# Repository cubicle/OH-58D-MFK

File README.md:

# OH-58D-MFK

[![CC BY-NC-SA 4.0][cc-by-nc-sa-shield]][cc-by-nc-sa]

## Work in progress

This project is still work in progress. Print and assemble at your own risk.

## BOM

-  1 x [Arduino Uno](https://www.amazon.de/Arduino-A000066-UNO-Rev3/dp/B008GRTSV6)
- 15 x [Heat Set Inserts M3x3 (short)](https://cnckitchen.store/products/heat-set-insert-m3-x-3-short-version-100-pieces)
-  4 x Heat Set Inserts M4
- 51 x [Diode SMD 0805 1N4148](https://www.ebay.de/itm/312738927547)
-  9 x [Resistor SMD 0805 10K](https://www.ebay.de/itm/362412320635)
- 47 x [OMRON B3F-115x Tactile Switch](https://www.ebay.de/itm/231954583799)
-  2 x [Switch cover](https://www.reichelt.de/de/de/shop/produkt/sicherheitsabdeckungen_fuer_kippschalter-105434)
-  2 x [Switch ON/OFF](https://www.pollin.de/p/kippschalter-kn3-c-101a-1-polig-on-off-420068)
-  1 x [Switch (ON)/OFF/(ON)](https://www.pollin.de/p/kippschalter-kn3-c-101a-1-polig-on-off-420068)
-  Break away pin headers
-  Wire
-  [Dupont crimping tool and connectors](https://www.amazon.de/dp/B07QX51F3B)
- 10 x Screw M3x0.50 x 8
-  5 x Screw M3x0.50 x 12

## 3D printed parts

### STLs

STLs are hosted on [Printables](https://www.printables.com/model/1201023-oh-58d-mfk).

### CAD

You can find the CAD files on [Onshape](https://cad.onshape.com/documents/6787d83c44a91f8cde39e86e/w/96151ec904b149525745d522/e/fceb9b6b394f6e8ffc93c401). Be careful as these may contain untested changes.

### Arduino Uno Case

You will need to print a case for the Arduino Uno. I used the [Arduino Uno Case](https://www.printables.com/model/122097-arduino-uno-case) from [Kazik](https://www.printables.com/@Kazik).

## License

Except where otherwise noted, this work © 2025 is licensed under a [Creative Commons Attribution-NonCommercial-ShareAlike 4.0 International License][cc-by-nc-sa].

[![CC BY-NC-SA 4.0][cc-by-nc-sa-image]][cc-by-nc-sa]

[cc-by-nc-sa]: http://creativecommons.org/licenses/by-nc-sa/4.0/
[cc-by-nc-sa-image]: https://licensebuttons.net/l/by-nc-sa/4.0/88x31.png
[cc-by-nc-sa-shield]: https://img.shields.io/badge/License-CC%20BY--NC--SA%204.0-lightgrey.svg

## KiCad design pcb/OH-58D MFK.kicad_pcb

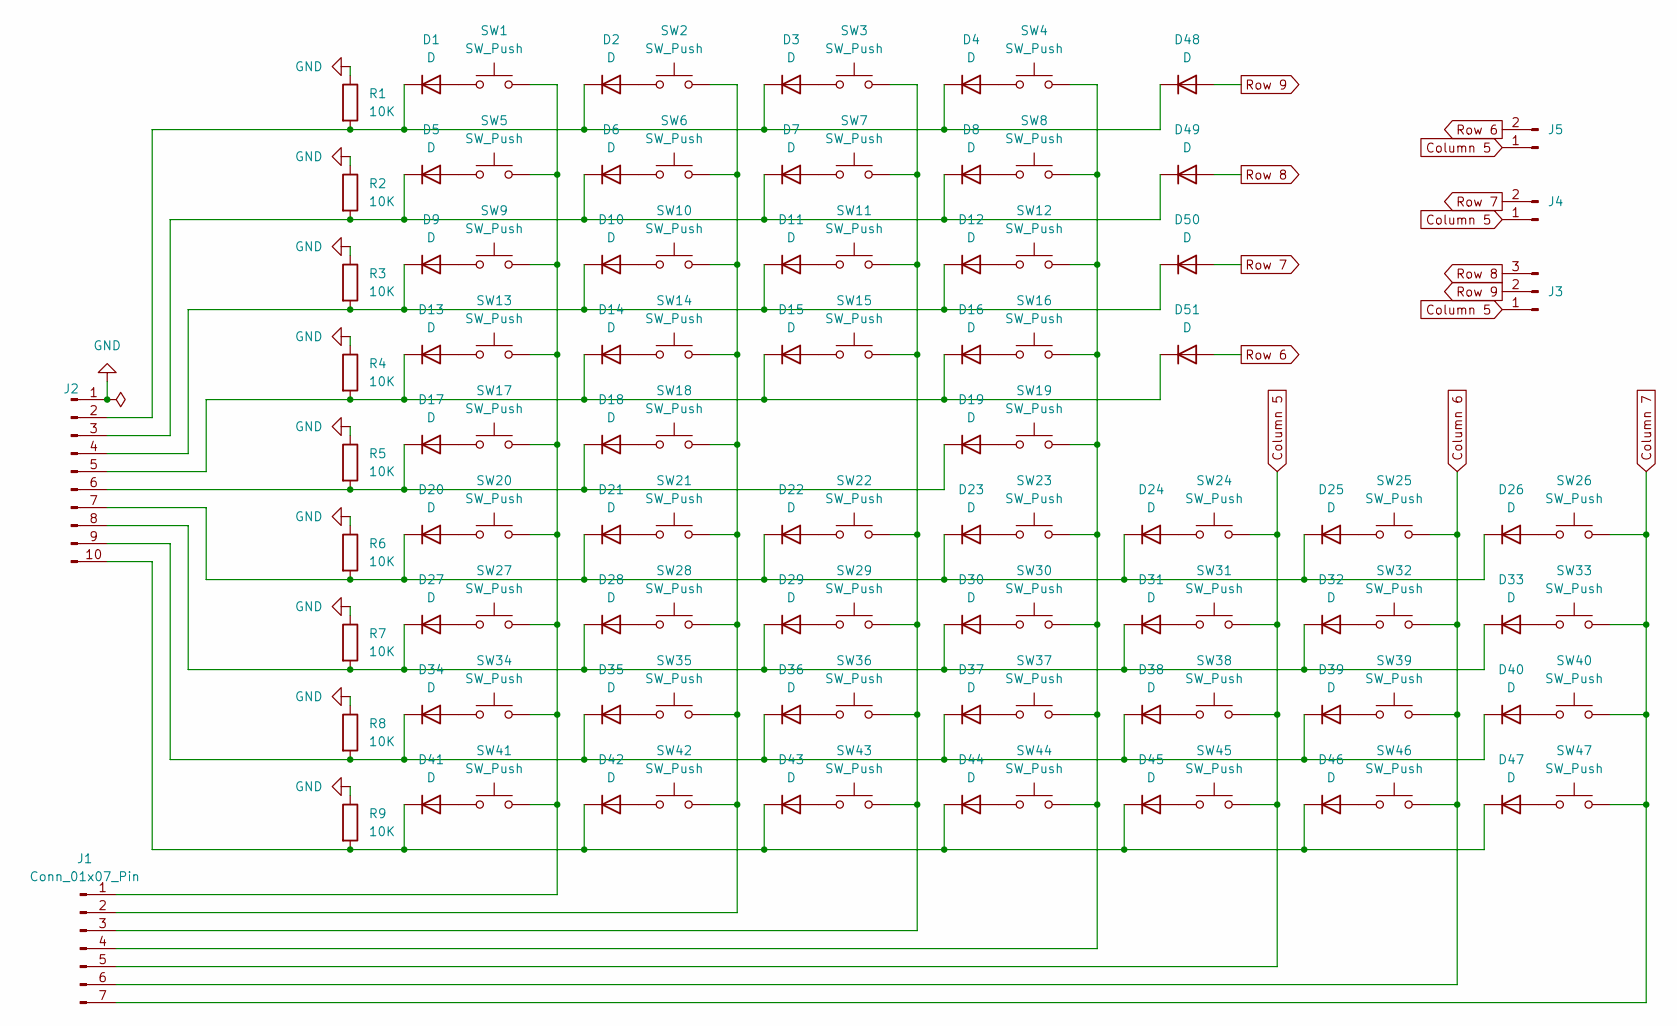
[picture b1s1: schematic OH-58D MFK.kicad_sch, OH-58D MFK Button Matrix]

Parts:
D1, D2, D3, D4, D5, D6, D7, D8, D9, D10, D11, D12, D13, D14, D15, D16, D17, D18, D19, D20, D21, D22, D23, D24, D25, D26, D27, D28, D29, D30, D31, D32, D33, D34, D35, D36, D37, D38, D39, D40, D41, D42, D43, D44, D45, D46, D47, D48, D49, D50, D51: D; D_0805_2012Metric_Pad1.15x1.40mm_HandSolder
J1: Conn_01x07_Pin; PinHeader_1x07_P2.54mm_Vertical
J2: Conn_01x10_Pin; PinHeader_1x10_P2.54mm_Vertical
J3: Conn_01x03_Pin; PinHeader_1x03_P2.54mm_Vertical
J4, J5: Conn_01x02_Pin; PinHeader_1x02_P2.54mm_Vertical
R1, R2, R3, R4, R5, R6, R7, R8, R9: 10K; R_0805_2012Metric_Pad1.20x1.40mm_HandSolder
SW1, SW2, SW3, SW4, SW5, SW6, SW7, SW8, SW9, SW10, SW11, SW12, SW13, SW14, SW15, SW16, SW17, SW18, SW19, SW20, SW21, SW22, SW23, SW24, SW25, SW26, SW27, SW28, SW29, SW30, SW31, SW32, SW33, SW34, SW35, SW36, SW37, SW38, SW39, SW40, SW41, SW42, SW43, SW44, SW45, SW46, SW47: SW_Push; SW_TH_Tactile_Omron_B3F-105x

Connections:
Column 5: J1.5, J3.1, J4.1, J5.1, SW24.2, SW31.2, SW38.2, SW45.2
Column 6: J1.6, SW25.2, SW32.2, SW39.2, SW46.2
Column 7: J1.7, SW26.2, SW33.2, SW40.2, SW47.2
GND: J2.1, R1.1, R2.1, R3.1, R4.1, R5.1, R6.1, R7.1, R8.1, R9.1
unnamed: D1.2 (A), SW1.1
unnamed: D1.1 (K), D2.1 (K), D3.1 (K), D4.1 (K), D48.1 (K), J2.2, R1.2
unnamed: D2.2 (A), SW2.1
unnamed: D3.2 (A), SW3.1
unnamed: D4.2 (A), SW4.1
unnamed: D5.2 (A), SW5.1
unnamed: D6.2 (A), SW6.1
unnamed: D7.2 (A), SW7.1
unnamed: D8.2 (A), SW8.1
unnamed: D9.2 (A), SW9.1
unnamed: D10.2 (A), SW10.1
unnamed: D9.1 (K), D10.1 (K), D11.1 (K), D12.1 (K), D50.1 (K), J2.4, R3.2
unnamed: D11.2 (A), SW11.1
unnamed: D12.2 (A), SW12.1
unnamed: D13.2 (A), SW13.1
unnamed: D13.1 (K), D14.1 (K), D15.1 (K), D16.1 (K), D51.1 (K), J2.5, R4.2
unnamed: D14.2 (A), SW14.1
unnamed: D15.2 (A), SW15.1
unnamed: D16.2 (A), SW16.1
unnamed: D17.2 (A), SW17.1
unnamed: D17.1 (K), D18.1 (K), D19.1 (K), J2.6, R5.2
unnamed: D18.2 (A), SW18.1
unnamed: D19.2 (A), SW19.1
unnamed: D20.2 (A), SW20.1
unnamed: D20.1 (K), D21.1 (K), D22.1 (K), D23.1 (K), D24.1 (K), D25.1 (K), D26.1 (K), J2.7, R6.2
unnamed: D21.2 (A), SW21.1
unnamed: D22.2 (A), SW22.1
unnamed: D23.2 (A), SW23.1
unnamed: D24.2 (A), SW24.1
unnamed: D25.2 (A), SW25.1
unnamed: D26.2 (A), SW26.1
unnamed: D27.2 (A), SW27.1
unnamed: D27.1 (K), D28.1 (K), D29.1 (K), D30.1 (K), D31.1 (K), D32.1 (K), D33.1 (K), J2.8, R7.2
unnamed: D28.2 (A), SW28.1
unnamed: D29.2 (A), SW29.1
unnamed: D30.2 (A), SW30.1
unnamed: D31.2 (A), SW31.1
unnamed: D32.2 (A), SW32.1
unnamed: D33.2 (A), SW33.1
unnamed: D34.2 (A), SW34.1
unnamed: D34.1 (K), D35.1 (K), D36.1 (K), D37.1 (K), D38.1 (K), D39.1 (K), D40.1 (K), J2.9, R8.2
unnamed: D35.2 (A), SW35.1
unnamed: D36.2 (A), SW36.1
unnamed: D37.2 (A), SW37.1
unnamed: D38.2 (A), SW38.1
unnamed: D39.2 (A), SW39.1
unnamed: D40.2 (A), SW40.1
unnamed: D41.2 (A), SW41.1
unnamed: D41.1 (K), D42.1 (K), D43.1 (K), D44.1 (K), D45.1 (K), D46.1 (K), D47.1 (K), J2.10, R9.2
unnamed: D42.2 (A), SW42.1
unnamed: D43.2 (A), SW43.1
unnamed: D44.2 (A), SW44.1
unnamed: D45.2 (A), SW45.1
unnamed: D46.2 (A), SW46.1
unnamed: D47.2 (A), SW47.1
unnamed: D5.1 (K), D6.1 (K), D7.1 (K), D8.1 (K), D49.1 (K), J2.3, R2.2
unnamed: J1.1, SW1.2, SW5.2, SW9.2, SW13.2, SW17.2, SW20.2, SW27.2, SW34.2, SW41.2
unnamed: J1.2, SW2.2, SW6.2, SW10.2, SW14.2, SW18.2, SW21.2, SW28.2, SW35.2, SW42.2
unnamed: J1.3, SW3.2, SW7.2, SW11.2, SW15.2, SW22.2, SW29.2, SW36.2, SW43.2
unnamed: J1.4, SW4.2, SW8.2, SW12.2, SW16.2, SW19.2, SW23.2, SW30.2, SW37.2, SW44.2
Row 6: D51.2 (A), J5.2
Row 7: D50.2 (A), J4.2
Row 8: D49.2 (A), J3.3
Row 9: D48.2 (A), J3.2

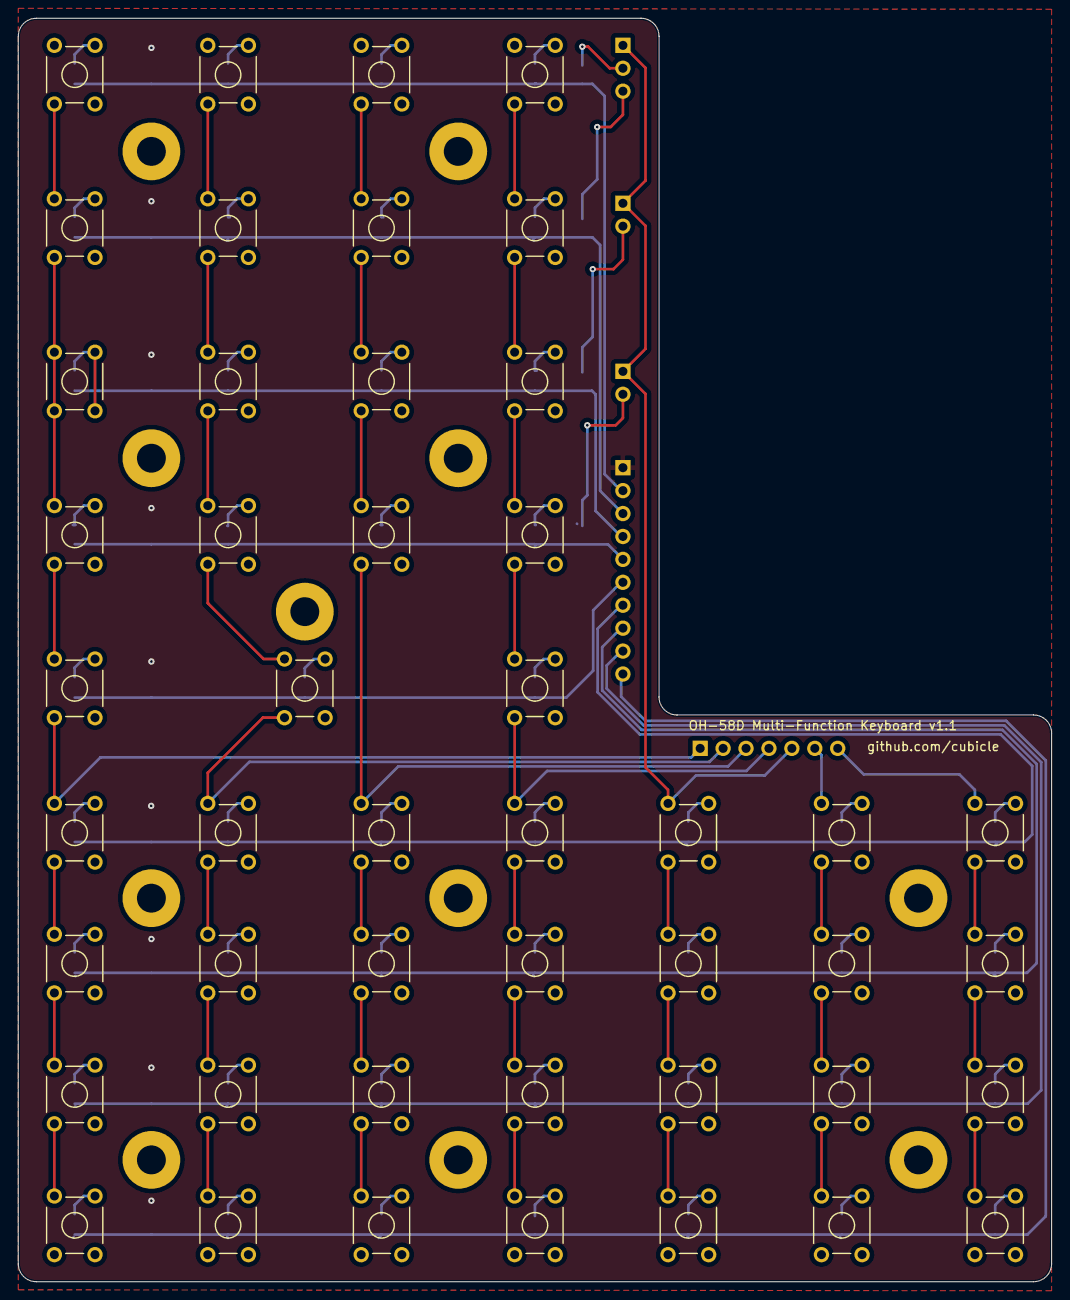
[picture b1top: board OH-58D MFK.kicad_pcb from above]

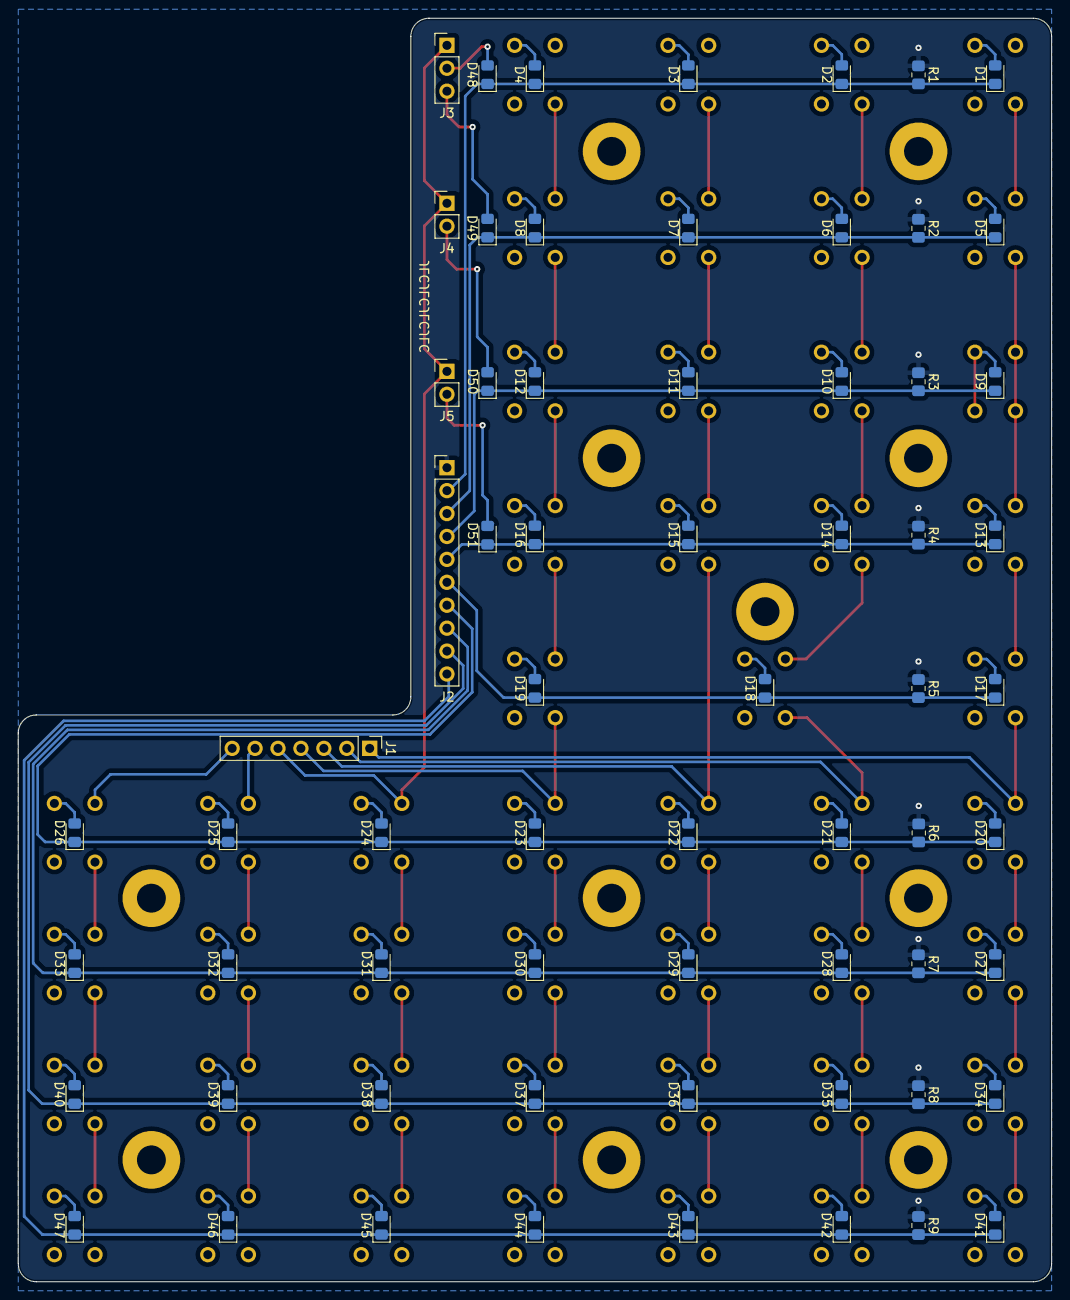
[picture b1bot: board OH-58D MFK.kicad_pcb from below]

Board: 2 copper layers, 114.5 x 140.0 mm, 112 parts (65 on the bottom side), 68 nets.

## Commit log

2025-01-05 Update .gitignore
    Add KiCAD specific folders to .gitignore
2025-01-05 Add KiCAD project files
2025-01-05 Add license information
2025-01-05 Add .gitignore entry to ignore downloaded PDF documents.
2025-01-05 Add .gitignore rule to ingore non public reference images
2025-01-05 Improve README by adding a link to the public Onshape document
2025-01-06 Improve PCB layout
    - Improve ground layer coverage
    - Increase JLCPCB order number size
    - Fix existing design rule errors
2025-01-06 Increase revision number to 1.0
2025-01-06 Fine tune tracks
2025-01-06 Fix minimal font thickness
2025-01-07 Change package size for diodes
    This commit also fixes silkscreen overlap warnings.
2025-01-07 fixup! Change package size for diodes
2025-01-07 Update footprints and change color
2025-01-07 Add project name, revision and author to pcb
2025-01-07 Update *.step file
2025-01-07 Enlarge vias
2025-01-07 Change pads for buttons
2025-01-07 Fix remaining via sizes to pass DFM rules
2025-01-07 Add design rules for JLCPCB from labtroll
2025-01-07 Fix some more silkscreen warnings
2025-01-07 Move diodes to get more clearance to pads
2025-01-07 Change footprint to increase pad to hole clearance
2025-01-08 Change version prefix
2025-01-08 Add image and warning to readme
2025-01-08 Initial PCB design 🚀
2025-01-27 Add missing trace for D44
2025-01-28 Add missing trace for D44 (#2)
2025-01-28 Raise PCB revision to 1.1
2025-02-01 Add source code to integrate panel with DCS Bios.
2025-02-01 Add basic BOM to README
2025-02-01 Add some missing parts to BOM
2025-02-01 Fix typo
2025-02-01 Add basic BOM to README (#3)
2025-02-01 Add source code to integrate panel with DCS Bios. (#4)
2025-02-21 Add link to Printables project to README
2025-02-21 Center align exploded view
2025-02-21 Center align exploded view (#5)
2025-07-24 Port code to be run on an Arduino Uno.
2025-07-24 Adds download instructions for the Arduino Uno case.
2025-07-24 Update image
